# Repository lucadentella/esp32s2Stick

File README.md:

# esp32s2Stick

## Description
esp32s2Stick is a USB device based on the **esp32-s2** chip by [Espressif](https://www.espressif.com/en/products/socs/esp32-s2).
Thanks to the presence of an USB OTG interface, it is possible to program the chip to act as a USB peripheral (*mass storage device*, *CDC*...) and to upgrade the firmware through USB (DFU, *Device Firmware Upgrade*).

In addition to the basic circuit needed to run the WROVER module, esp32s2Stick offers an **RGB LED** and a socket for **MicroSD** cards.
## How to make
- Blog post on [my website](http://www.lucadentella.it/en/2021/02/16/esp32s2stick/)
- Eagle files (schematic and board) are available in the "**eagle**" subfolder
- Some test *sketches* for Arduino are available in the "**arduino**" subfolder
- PCB can be ordered [from PCBWay](https://www.pcbway.com/project/shareproject/esp32s2Stick.html)
## Partlist 
 - **C1, C2**: 100nF SMD capacitor (0805)
 - **C3, C4**: 1uF SMD capacitor (0805)
 - **R1, R2, R3, R4, R5, R6**: 10Kohm SMD resistor (0603)
 - **IC1**: 1117-3.3 voltage regulator
 - **D1**: WS2812 RGB led (5050, 4 pins)
 - **BOOT, EN**: SMD momentary switch (5.2mm)
 - **U1**: ESP32-S2-WROVER
 - **J1**: USB A male SMD connector
 - **P1**: MicroSD card socket

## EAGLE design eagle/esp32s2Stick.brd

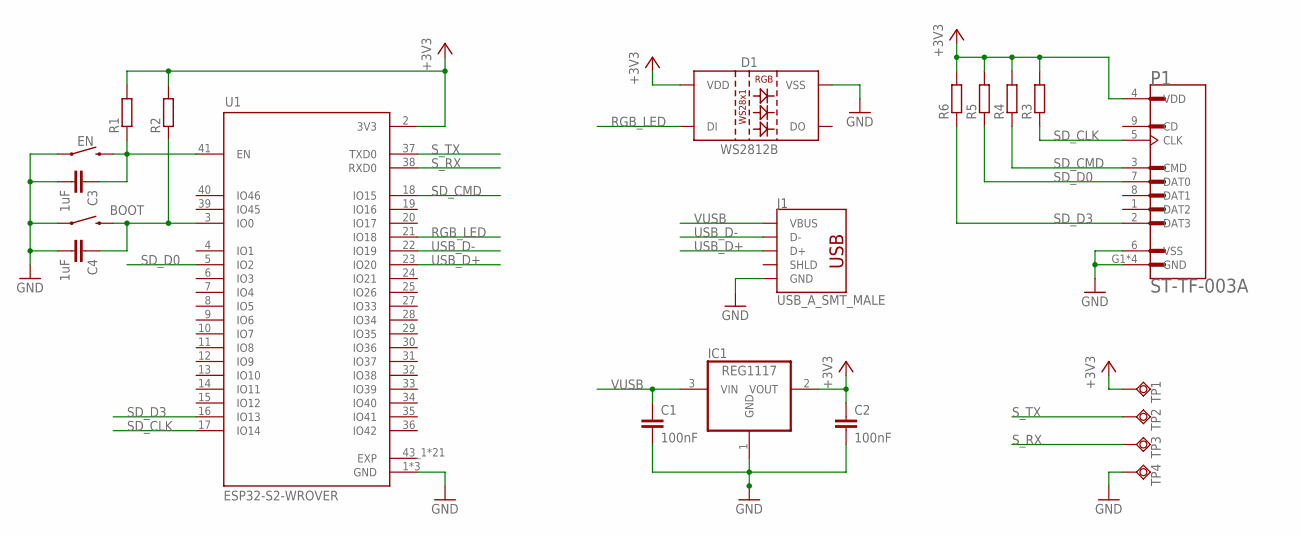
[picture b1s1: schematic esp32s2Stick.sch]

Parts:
BOOT: MOMENTARY-SWITCH-SPST-SMD-5.2MM; TACTILE_SWITCH_SMD_5.2MM
C1, C2: 100nF; C0805
C3, C4: 1uF; C0805
D1: WS2812B
EN: MOMENTARY-SWITCH-SPST-SMD-5.2MM; TACTILE_SWITCH_SMD_5.2MM
IC1: REG1117; SOT223
J1: USB_A_SMT_MALE; USB-A-SMT-MALE
P1: ST-TF-003A; SUNTECH_ST-TF-003A
R1, R2, R3, R4, R5, R6: R-EU_R0603; R0603
TP1, TP2, TP3, TP4: TPSQTP15R; TP15R
U1: ESP32-S2-WROVER; MODULE_ESP32-S2-WROVER

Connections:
+3V3: C2.1, D1.1 (VDD), IC1.2 (VOUT), P1.4 (VDD), R1.2, R2.2, R3.2, R4.2, R5.2, R6.2, TP1.TP, U1.2 (3V3)
EXP: U1.43_1 (EXP), U1.43_2 (EXP), U1.43_3 (EXP), U1.43_4 (EXP), U1.43_5 (EXP), U1.43_6 (EXP), U1.43_7 (EXP), U1.43_8 (EXP), U1.43_9 (EXP), U1.43_10 (EXP), U1.43_11 (EXP), U1.43_12 (EXP), U1.43_13 (EXP), U1.43_14 (EXP), U1.43_15 (EXP), U1.43_16 (EXP), U1.43_17 (EXP), U1.43_18 (EXP), U1.43_19 (EXP), U1.43_20 (EXP), U1.43_21 (EXP)
GND: BOOT.1, C1.2, C2.2, C3.2, C4.2, D1.3 (VSS), EN.1, IC1.1 (GND), J1.GND1 (GND), P1.6 (VSS), P1.G1 (GND), P1.G2 (GND), P1.G3 (GND), P1.G4 (GND), TP4.TP, U1.1 (GND), U1.26 (GND), U1.42 (GND)
unnamed: BOOT.3 (2), C4.1, R2.1, U1.3 (IO0)
unnamed: C3.1, EN.3 (2), R1.1, U1.41 (EN)
RGB_LED: D1.4 (DI), U1.21 (IO18)
SD_CLK: P1.5 (CLK), R3.1, U1.17 (IO14)
SD_CMD: P1.3 (CMD), R4.1, U1.18 (IO15)
SD_D0: P1.7 (DAT0), R5.1, U1.5 (IO2)
SD_D3: P1.2 (DAT3), R6.1, U1.16 (IO13)
S_RX: TP3.TP, U1.38 (RXD0)
S_TX: TP2.TP, U1.37 (TXD0)
USB_D+: J1.D+1 (D+), U1.23 (IO20)
USB_D-: J1.D-1 (D-), U1.22 (IO19)
VUSB: C1.1, IC1.3 (VIN), J1.VBUS1 (VBUS)

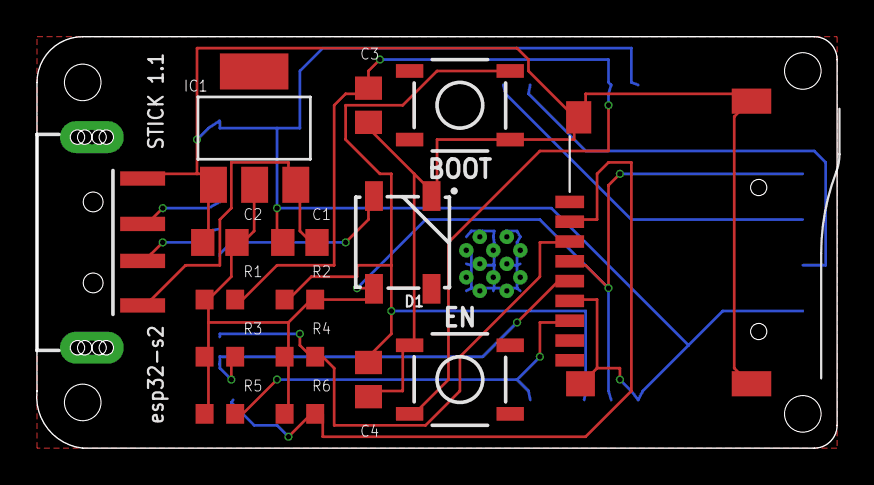
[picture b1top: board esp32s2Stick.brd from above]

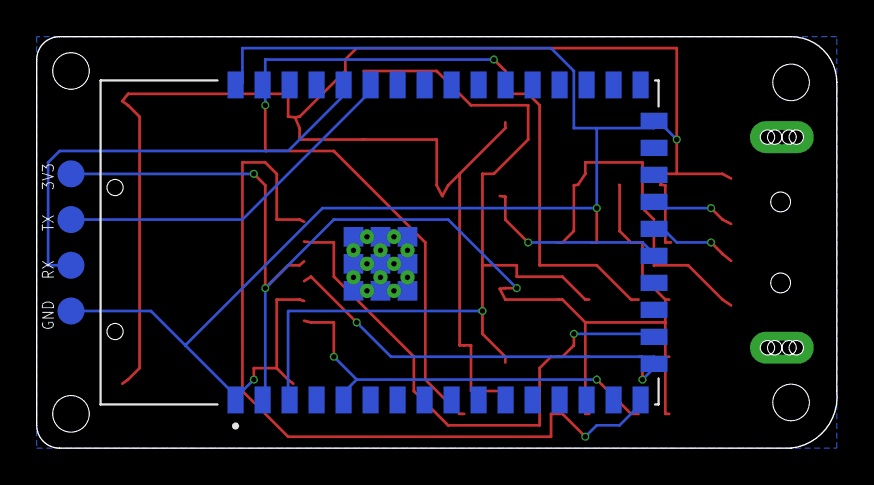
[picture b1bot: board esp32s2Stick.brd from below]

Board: 2 copper layers, 44.5 x 22.9 mm, 21 parts (5 on the bottom side), 15 nets.

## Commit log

2021-02-16 Add license
2021-02-16 Eagle files added
2021-02-16 Readme updated
2021-02-16 Images added
2021-02-16 Arduino examples added
2021-02-16 Readme updated with blog post

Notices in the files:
parts and their libraries:
SparkFun-Switches: Licensing: Creative Commons ShareAlike 4.0 International - https://creativecommons.org/licenses/by-sa/4.0
